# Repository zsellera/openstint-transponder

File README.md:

# OpenStint transponder reference design

RC (surface) racing transponder with STM32C011, featuring:
* OpenStint protocol reference implentation (this is not an RC3 clone!)
* 5 MHz BPSK using SPI MOSI
* MOSFET driver repurposed as a high-current source for the antenna coil
* Tuned antenna, signal level is ca. 50% of the commercial deal when measured with a smallish near-field H-probe.
* Reverse polarity protection
* Power line filtering (TODO: LISN measurements....)
* LCSC product codes added.

**Related projects:** [OpenStint decoder with HackRF One](https://github.com/zsellera/openstint) | [Loop Amplifier](https://github.com/zsellera/openstint-preamp)

JLCPCB manifactures and assembles 5 panels of 2x4s, grand total of 40 pcs, for $130, including taxes and shipping.

## Compile & flash

The firmware compiles with cmake (and downloads the necessary STM32 libraries meanwhile). Make sure to use `Release` build: creating the BPSK signal with the right timing is critical, and `-O0` optimalization level does not guarantee that. If you see signal coming out from the transponder, but it can not be decoded, this should be the first thing to check.

```shell
cmake -DCMAKE_BUILD_TYPE=Release .
make

st-flash --connect-under-reset --format ihex write transponder.hex
```

The programming points are separated by 2 mm. I use a pinheader of the same pitch with pogo pins attached to them as a makeshift programming adapter.

[programming jig by Durtman](https://www.thingiverse.com/thing:7310937)

## Personal note (2025-12-10)

This project use a FET driver from TI to produce the necessary antenna current. This IC needs 4.5 V minimum to operate, meaning we can not use this transponder with 1s batteries (1/12 pancars). I could not find any push-pull driver which can operate at 3.3 V and 5+ MHz. Some MCUs exists which can source/sink 50 mA directly from GPIO, but as of now, I don't know how to make this transponder work with such a low current. This design requires ±170 mA, and still produces only 1/2 of the signal level as an RC4 hybrid.

Having a design that works with 50 mA would have benefits, like:
* 1s battery support
* LDO integrated with reverse battery protection (reduced component count)
* No need of UCC27517 driver (reduced component count)
* Fewer components perpendicular to the magnetic field (reduced eddys)

Unfortunately, I do not have the required analog brain to figure this out. I feel we should move to a 6-layer board: the `docs/antenna2.asc` ltspice sim suggests that increasing the turn count reduces the peak current less than the extra turns contribute to the magnetic moment (`~N*I*A`). Unfortunately, this is just a guess, and I'm not really enjoying the development based on trial-and-error.

**UPDATE 2025-12-11:** I kept reading on NFC and alike topics. I think there are two ways forward:

1. Keep the current design, it's not that bad after all. I see 3 areas for improvement: signal conditioniong (not sinusoidal enough), signal strength (minor problem) and board space (also minor). We can push the gate driver a bit further, up to the 4-500 mA range (I've done that before), solving the signal strength problem. Most NFC designs I've seen adds some LC-network between the push-pull stage and the antenna's LC-tank (improving both on power transfer and spectral purity). By removing the antenna loop from the top layer we can gain some board space (layer 2..4 should have 3-3-3 loops, 9 in total). We can move the components on top layer above the antenna wires, where the magnetic field is less perpendicular to the components (less eddy, more board space). No need for 6 layers. On the negative side, it can't support 1s batteries :(.
2. Experiment with a totally different topology. The current limitation after all is the current which the FET driver can safely push through the antenna loop. Any phase difference between the driving signal and the LC-tank forces the driving current to go extreme. This is less of a problem with a single discrete transistor. If we add (+) a positive feedback from the LC-tank to the control signal of the MCU, we can approximate zero-voltage switching. By tuning the feedback*amplification to below-1, only the control signal could bring the circuit into oscillation. I'm looking at you, [Meissner oscillator](https://en.wikipedia.org/wiki/Armstrong_oscillator)... 

## Manufacting

See [relases](https://github.com/zsellera/openstint-transponder/releases/) for gerber, pos and BOM files. These are directly uploadable to [JLCPCB](https://jlcpcb.com/). As of now (2025-12-10), manufacturing 5 panels (40 transponders) with assembly costs $160, while 20 panels (160 pcs of transponders) cost $300 (prices with shipping and taxes to EU).

Manufacture with 1 mm PCB width (so coil tuning matches mine).

```
kikit panelize \
    --layout 'hspace: 3mm; vspace: 3mm; rows: 4; cols: 2' \
    --tabs 'type: fixed; vwidth: 4mm; hwidth: 4mm; vcount: 0' \
    --cuts 'type: mousebites; offset: -0.25mm' \
    --framing 'type: frame; hspace: 3mm; vspace: 3mm; width: 4mm' \
    --post 'millradius: 1.5mm' \
    ...
```

```
kikit fab jlcpcb --assembly --schematic ./openstint-transponder.kicad_sch ./panel/panel-8.kicad_pcb panel/
```

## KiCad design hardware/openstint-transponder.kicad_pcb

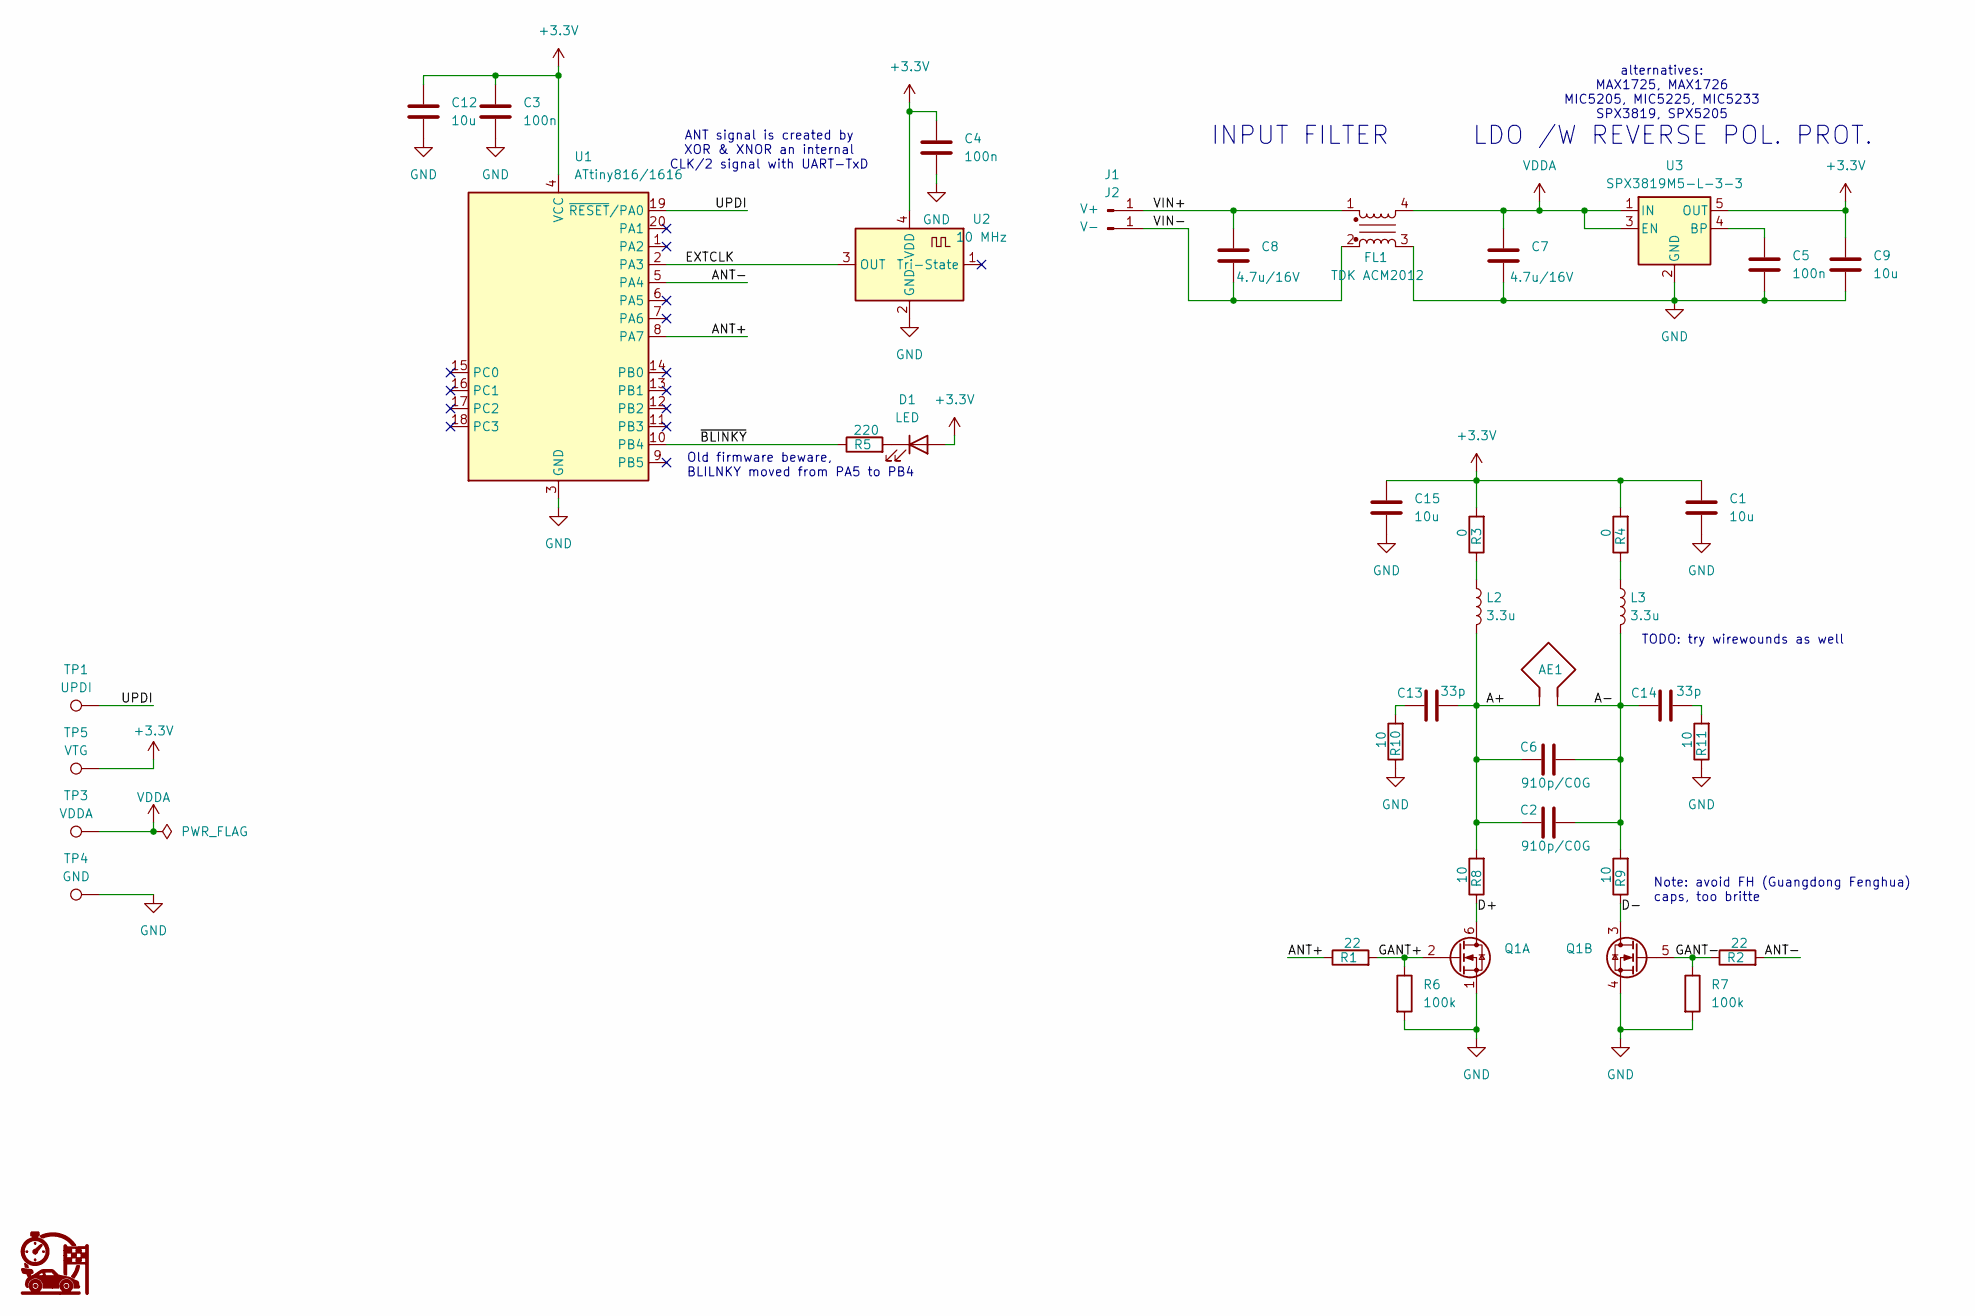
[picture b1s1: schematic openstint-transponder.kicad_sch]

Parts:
AE1: Antenna_Loop
C1, C9, C12, C15: 10u; C_0402_1005Metric; LCSC C15525
C2, C6: 910p/C0G; C_0402_1005Metric; LCSC C2941944
C3, C4, C5: 100n; C_0402_1005Metric; LCSC C1525
C7, C8: 4.7u/16V; C_0603_1608Metric; LCSC C19666
C13, C14: 33p; C_0402_1005Metric; LCSC C1562
D1: LED; LED_0603_1608Metric; LCSC C2286
FL1: TDK ACM2012; ACM2012; LCSC C76571
G1: SYM_OpenStint; openstint-logo_12x12
J1: V+; SolderWirePad_1x01_SMD_1x2mm
J2: V-; SolderWirePad_1x01_SMD_1x2mm
L2, L3: 3.3u; L_0603_1608Metric; LCSC C162581
Q1: PMGD280UN; SOT-363_SC-70-6; LCSC C135817
R1, R2: 22; R_0402_1005Metric; LCSC C25092
R3, R4: 0; R_0402_1005Metric; LCSC C17168
R5: 220; R_0402_1005Metric; LCSC C25091
R6, R7: 100k; R_0402_1005Metric; LCSC C25741
R8, R9, R10, R11: 10; R_0402_1005Metric; LCSC C25077
TP1: UPDI; TestPoint_Pad_D1.0mm
TP3: VDDA; TestPoint_Pad_D1.0mm
TP4: GND; TestPoint_Pad_D1.0mm
TP5: VTG; TestPoint_Pad_D1.0mm
U1: ATtiny816/1616; VQFN-20-1EP_3x3mm_P0.4mm_EP1.7x1.7mm; LCSC C2052778
U2: 10 MHz; Crystal_SMD_3225-4Pin_3.2x2.5mm; LCSC C2831380
U3: SPX3819M5-L-3-3; SOT-23-5; LCSC C9055

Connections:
+3.3V: C1.1, C3.2, C4.2, C9.1, C12.1, C15.1, D1.2 (A), R3.2, R4.2, TP5.1, U1.4 (VCC), U2.4 (VDD), U3.5 (OUT)
/A+: AE1.1, C2.1, C6.1, C13.2, L2.2, R8.2
/A-: AE1.2, C2.2, C6.2, C14.1, L3.2, R9.2
/ANT+: R1.1, U1.8 (PA7)
/ANT-: R2.2, U1.5 (PA4)
/D+: Q1.6 (D), R8.1
/D-: Q1.3 (D), R9.1
/EXTCLK: U1.2 (PA3), U2.3 (OUT)
/GANT+: Q1.2 (G), R1.2, R6.1
/GANT-: Q1.5 (G), R2.1, R7.1
/UDPI: TP1.1, U1.19 (~RESET/PA0)
/VIN+: C8.1, FL1.1, J1.1
/VIN-: C8.2, FL1.2, J2.1
/~BLINKY: R5.1, U1.10 (PB4)
GND: C1.2, C3.1, C4.1, C5.2, C7.2, C9.2, C12.2, C15.2, FL1.3, Q1.1 (S), Q1.4 (S), R6.2, R7.2, R10.1, R11.1, TP4.1, U1.3 (GND), U1.21 (GND), U2.2 (GND), U3.2 (GND)
unnamed: C13.1, R10.2
unnamed: C14.2, R11.2
unnamed: D1.1 (K), R5.2
unnamed: L2.1, R3.1
unnamed: L3.1, R4.1
unnamed: C5.1, U3.4 (BP)
VDDA: C7.1, FL1.4, TP3.1, U3.1 (IN), U3.3 (EN)

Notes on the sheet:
Note: avoid FH (Guangdong Fenghua) caps, too britte
Old firmware beware, BLILNKY moved from PA5 to PB4
TODO: try wirewounds as well
alternatives: MAX1725, MAX1726 MIC5205, MIC5225, MIC5233 SPX3819, SPX5205
INPUT FILTER
ANT signal is created by XOR & XNOR an internal CLK/2 signal with UART-TxD
LDO /W REVERSE POL. PROT.

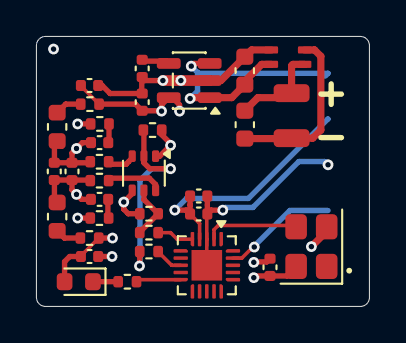
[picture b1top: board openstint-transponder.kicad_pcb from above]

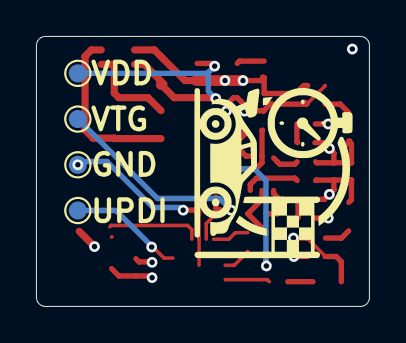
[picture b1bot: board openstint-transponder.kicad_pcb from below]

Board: 4 copper layers, 18.5 x 15.0 mm, 39 parts (5 on the bottom side), 22 nets.

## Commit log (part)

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2025-11-11 firmware added
2025-11-11 image added to readme
2025-12-10 antenna re-tuned
2025-12-10 readme update
2025-12-11 readme: add notes on possible improvements
2026-01-22 README: compile and flash instructions
2026-03-11 v2 transponder
2026-03-23 v2 transponder - initial commit
2026-03-23 github workflow to automatically create a release
2026-03-23 panelize pcb workflow
2026-03-23 Revert "v2 transponder"
    This reverts commit ef6581161f0553e0c47b9335515ce2e00a666ec4.
2026-03-23 workflow file from master
2026-04-12 avr - test firmware
2026-04-13 v2 avr firmware
2026-04-17 spin v2
2026-04-19 use 2x tuning caps
2026-04-19 fine-tune snubber values
2026-05-20 firmware for attiny816
2026-05-20 remove old stm32 firmware
2026-05-20 nightly builds firmware as well
2026-05-20 updated documentation
2026-05-20 README: v2 images and information
2026-05-25 order placement guide linked
2026-05-26 programming jig link
2026-06-16 switch to internal 20 MHz on CMOS clock failure
2026-06-17 init sequence fix
2026-06-17 nightly build to cmake
